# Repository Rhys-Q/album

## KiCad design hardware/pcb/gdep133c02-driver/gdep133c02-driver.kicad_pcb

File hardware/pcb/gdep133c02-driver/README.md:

# GDEP133C02 驱动板 v0.11

当前工程采用用户指定的17组基础库原型方案：147件、145个顶面SMD，其中138个机器贴片、9个手工装配，36组采购型号；100×80mm四层及接口位置保持。3组参数审核通过，14组电气等效未验证。

[改版及验证边界](docs/基础库17组改版-v0.11.md)、[采购清单](docs/采购清单-v0.11.csv)、[逐位号对照](docs/逐位号替换对照-v0.11.csv)、[剩余例外](docs/17组决定及剩余例外-v0.11.csv)。基础库组合补充页 basic-composites.kicad_sch 通过原工程入口加载；原有符号UUID保留。

当前制造审阅包：[v0.11](releases/jlc-cn-review-v0.11-basic17-2026-10-11/README.md)，ERC、DRC、未连接、一致性均为0；KiCad实际更新/保存后无重复新增或待执行变更。实板显示、瞬态、温升、FPC配接及安全掉电尚未验收，C15008 SMT库存仍未知。KiCad10.0.6。

学习资料：[学习指南](docs/learning-guide.md)、[电源](docs/power-circuit-explained.md)、[接口](docs/interface-circuit-explained.md)、[屏幕](docs/panel-circuit-explained.md)。旧v0.9/v0.10文档为历史快照。

2026-10-11装配调整：用户淘宝采购U4/U5/Q3/D3/D5/D6/FPC1并手焊；仅改变机器BOM/CPL分配，电路、PCB和Gerber保持。以assembly-plan.json为当前导出装配规则，CAD中的SMT属性描述此前装配方式。

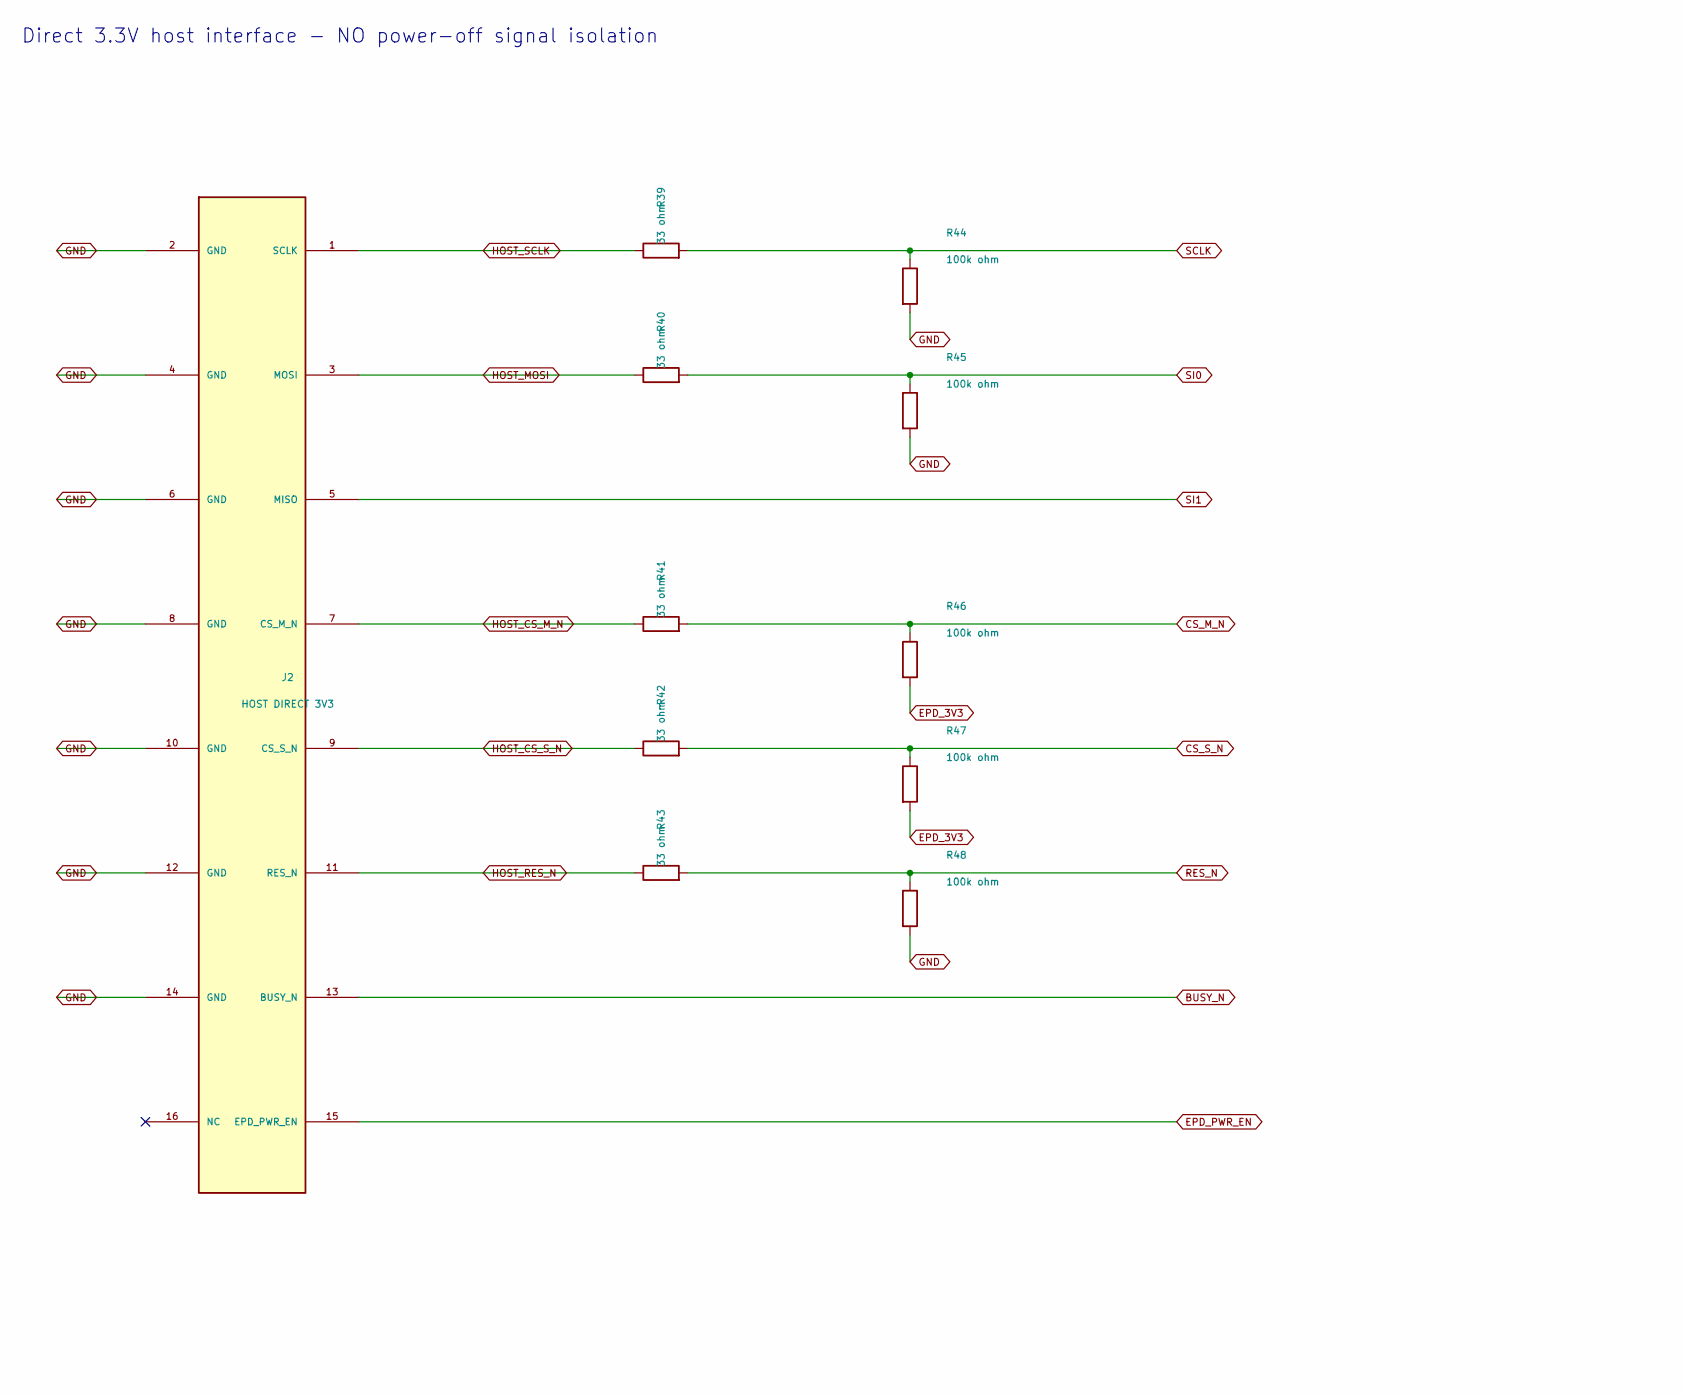
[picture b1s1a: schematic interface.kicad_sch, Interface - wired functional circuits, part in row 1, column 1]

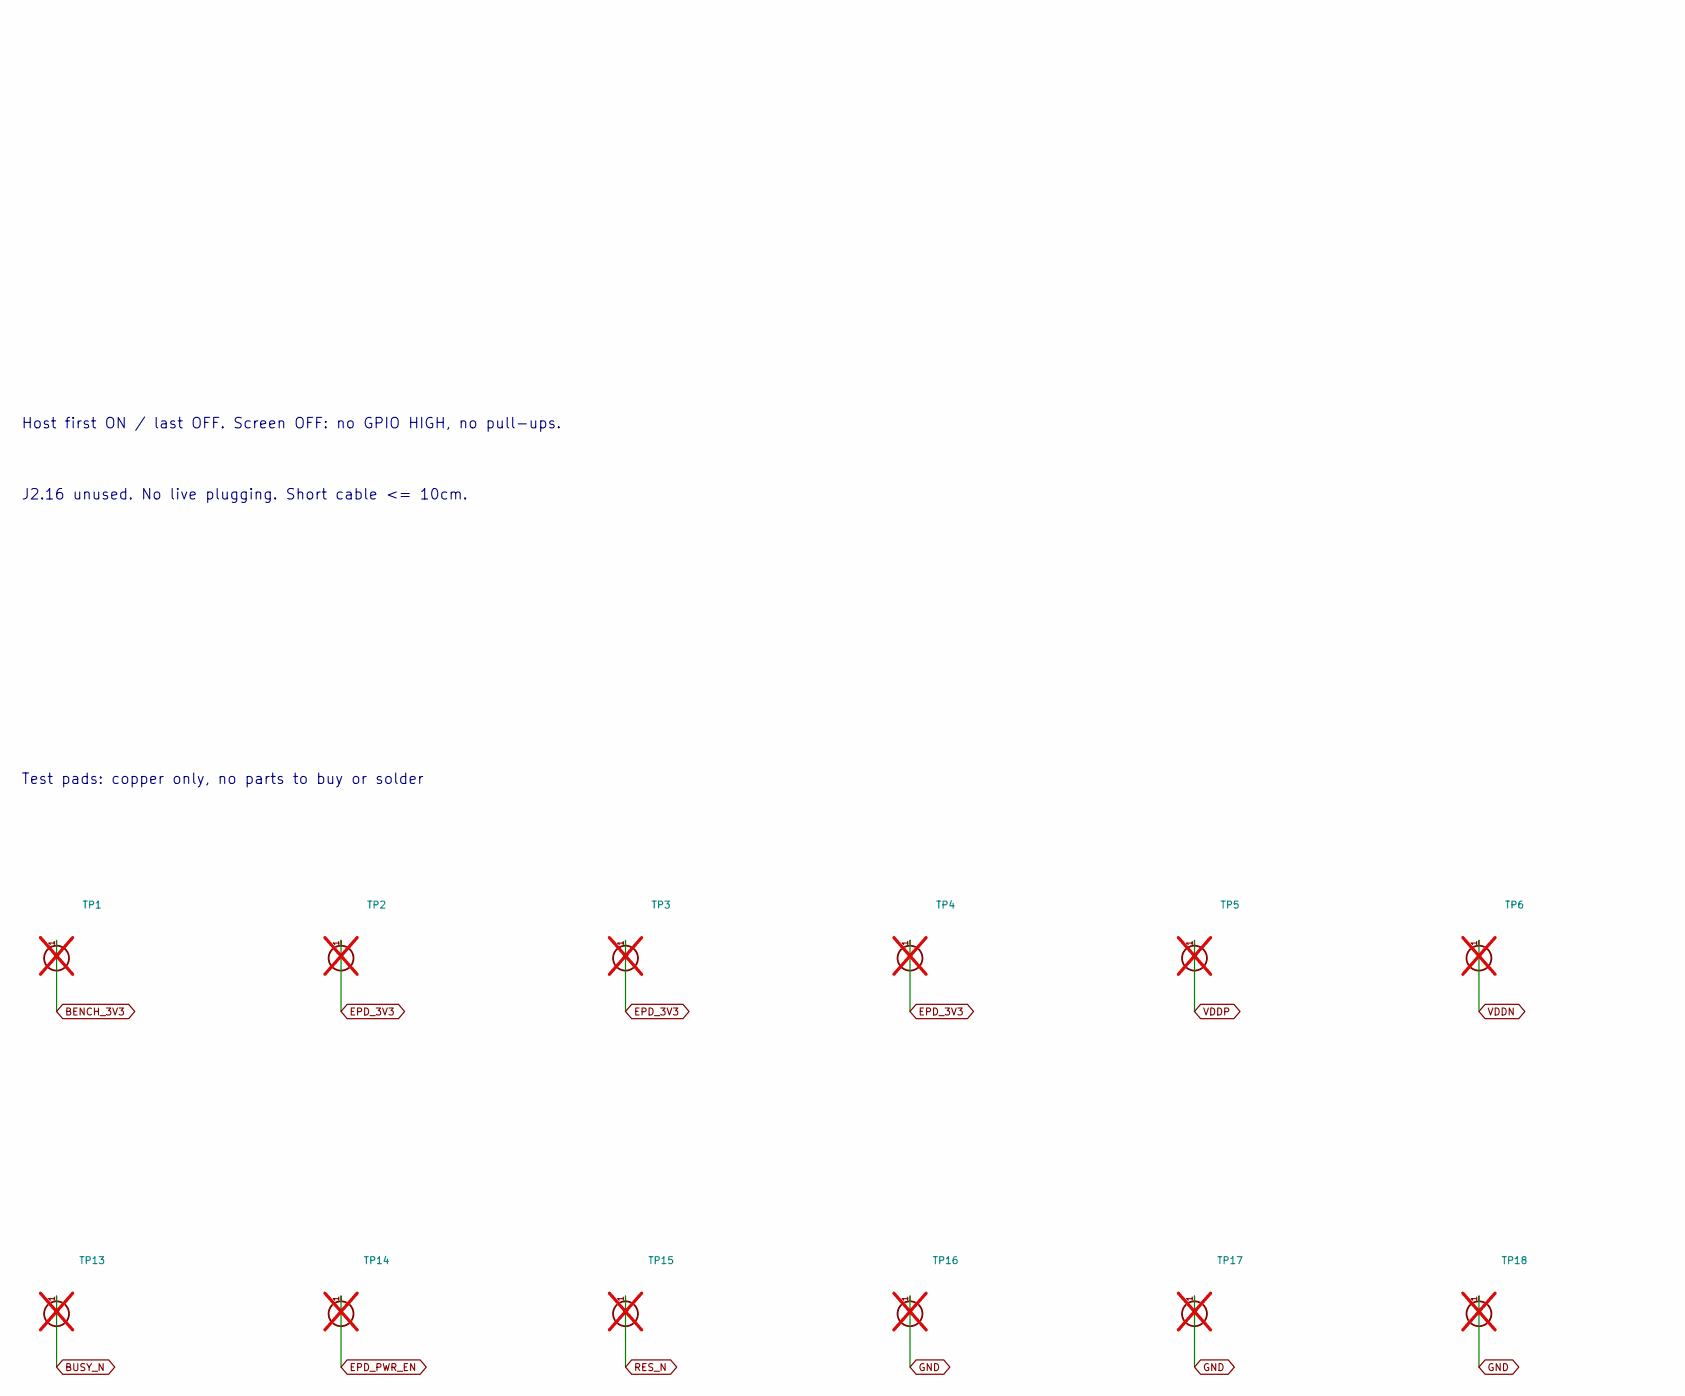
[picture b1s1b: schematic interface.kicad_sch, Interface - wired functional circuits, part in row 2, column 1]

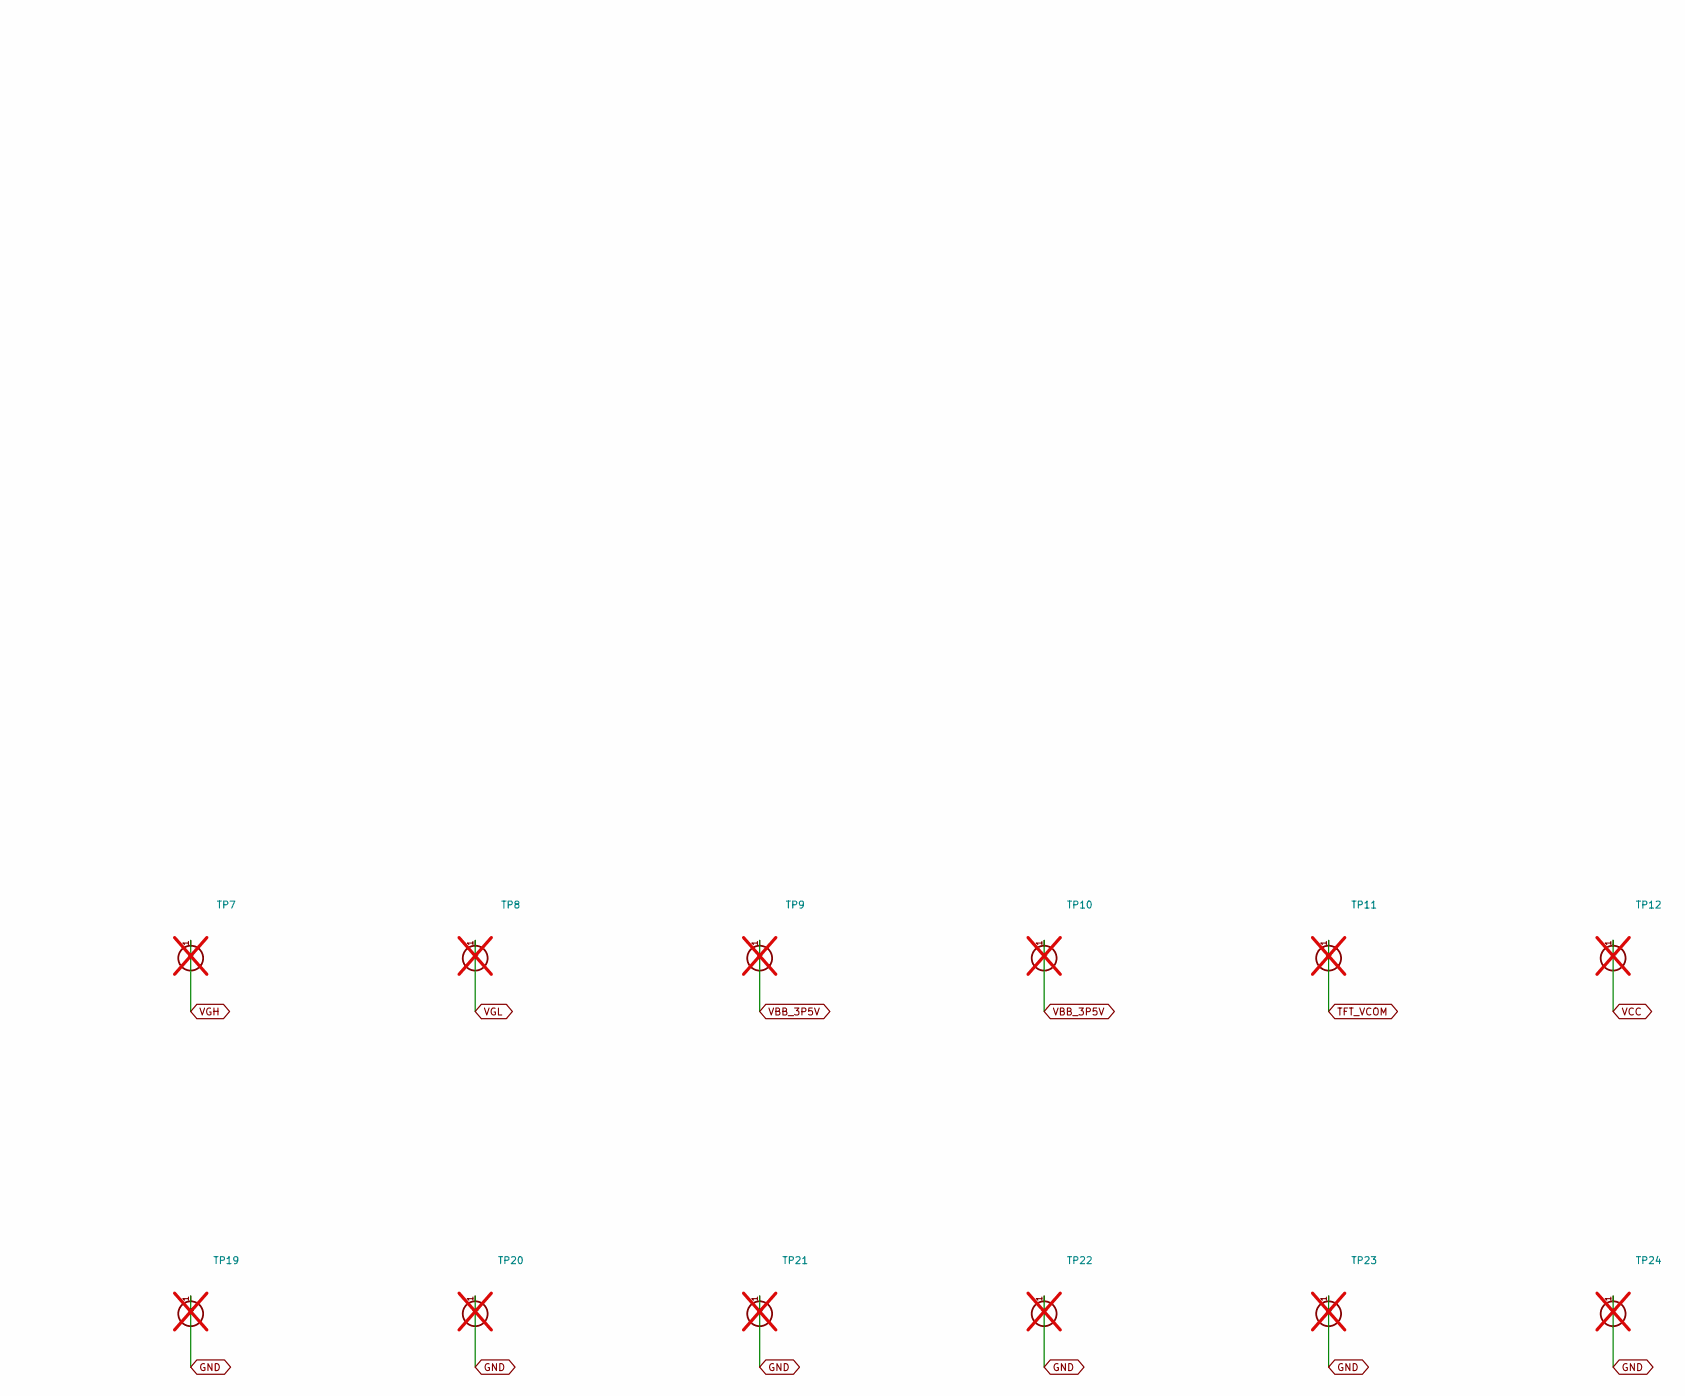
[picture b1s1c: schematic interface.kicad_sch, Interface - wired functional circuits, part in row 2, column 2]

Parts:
J2: HOST DIRECT 3V3; Connector_PinHeader_2.54mm__PinHeader_2x08_P2.54mm_Vertical; MPN SH-PZ254V-2x8P; LCSC C55629829
R39, R40, R41, R42, R43: 33 ohm; R_0805_HandSolder; MPN 0805W8F330JT5E; LCSC C17634
R44, R45, R46, R47, R48: 100k ohm; R_0805_HandSolder; MPN 0805W8F1003T5E; LCSC C149504
TP1: BENCH_3V3; TestPoint__TestPoint_Pad_D1.5mm; MPN PCB test pad; not fitted
TP2, TP3, TP4: EPD_3V3; TestPoint__TestPoint_Pad_D1.5mm; MPN PCB test pad; not fitted
TP5: VDDP; TestPoint__TestPoint_Pad_D1.5mm; MPN PCB test pad; not fitted
TP6: VDDN; TestPoint__TestPoint_Pad_D1.5mm; MPN PCB test pad; not fitted
TP7: VGH; TestPoint__TestPoint_Pad_D1.5mm; MPN PCB test pad; not fitted
TP8: VGL; TestPoint__TestPoint_Pad_D1.5mm; MPN PCB test pad; not fitted
TP9: VBB_3P5V; TestPoint__TestPoint_Pad_D1.5mm; MPN PCB test pad; not fitted
TP10: VNCP_3P5V; TestPoint__TestPoint_Pad_D1.5mm; MPN PCB test pad; not fitted
TP11: TFT_VCOM; TestPoint__TestPoint_Pad_D1.5mm; MPN PCB test pad; not fitted
TP12: VCC; TestPoint__TestPoint_Pad_D1.5mm; MPN PCB test pad; not fitted
TP13: BUSY_N; TestPoint__TestPoint_Pad_D1.5mm; MPN PCB test pad; not fitted
TP14: EPD_PWR_EN; TestPoint__TestPoint_Pad_D1.5mm; MPN PCB test pad; not fitted
TP15: RES_N; TestPoint__TestPoint_Pad_D1.5mm; MPN PCB test pad; not fitted
TP16, TP17, TP18, TP19, TP20, TP21, TP22, TP23, TP24: GND; TestPoint__TestPoint_Pad_D1.5mm; MPN PCB test pad; not fitted

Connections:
BENCH_3V3: TP1.1 (1_1); also elsewhere on the board
BUSY_N: J2.13 (BUSY_N), TP13.1 (1_1); also elsewhere on the board
CS_M_N: R41.2, R46.1; also elsewhere on the board
CS_S_N: R42.2, R47.1; also elsewhere on the board
EPD_3V3: R46.2, R47.2, TP2.1 (1_1), TP3.1 (1_1), TP4.1 (1_1); also elsewhere on the board
EPD_PWR_EN: J2.15 (EPD_PWR_EN), TP14.1 (1_1); also elsewhere on the board
GND: J2.2 (GND), J2.4 (GND), J2.6 (GND), J2.8 (GND), J2.10 (GND), J2.12 (GND), J2.14 (GND), R44.2, R45.2, R48.2, TP16.1 (1_1), TP17.1 (1_1), TP18.1 (1_1), TP19.1 (1_1), TP20.1 (1_1), TP21.1 (1_1), TP22.1 (1_1), TP23.1 (1_1), TP24.1 (1_1); also elsewhere on the board
HOST_CS_M_N: J2.7 (CS_M_N), R41.1
HOST_CS_S_N: J2.9 (CS_S_N), R42.1
HOST_MOSI: J2.3 (MOSI), R40.1
HOST_RES_N: J2.11 (RES_N), R43.1
HOST_SCLK: J2.1 (SCLK), R39.1
RES_N: R43.2, R48.1, TP15.1 (1_1); also elsewhere on the board
SCLK: R39.2, R44.1; also elsewhere on the board
SI0: R40.2, R45.1; also elsewhere on the board
SI1: J2.5 (MISO); also elsewhere on the board
TFT_VCOM: TP11.1 (1_1); also elsewhere on the board
VBB_3P5V: TP9.1 (1_1), TP10.1 (1_1); also elsewhere on the board
VCC: TP12.1 (1_1); also elsewhere on the board
VDDN: TP6.1 (1_1); also elsewhere on the board
VDDP: TP5.1 (1_1); also elsewhere on the board
VGH: TP7.1 (1_1); also elsewhere on the board
VGL: TP8.1 (1_1); also elsewhere on the board

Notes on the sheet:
Direct 3.3V host interface - NO power-off signal isolation
Host first ON / last OFF. Screen OFF: no GPIO HIGH, no pull-ups.
J2.16 unused. No live plugging. Short cable <= 10cm.
Test pads: copper only, no parts to buy or solder
